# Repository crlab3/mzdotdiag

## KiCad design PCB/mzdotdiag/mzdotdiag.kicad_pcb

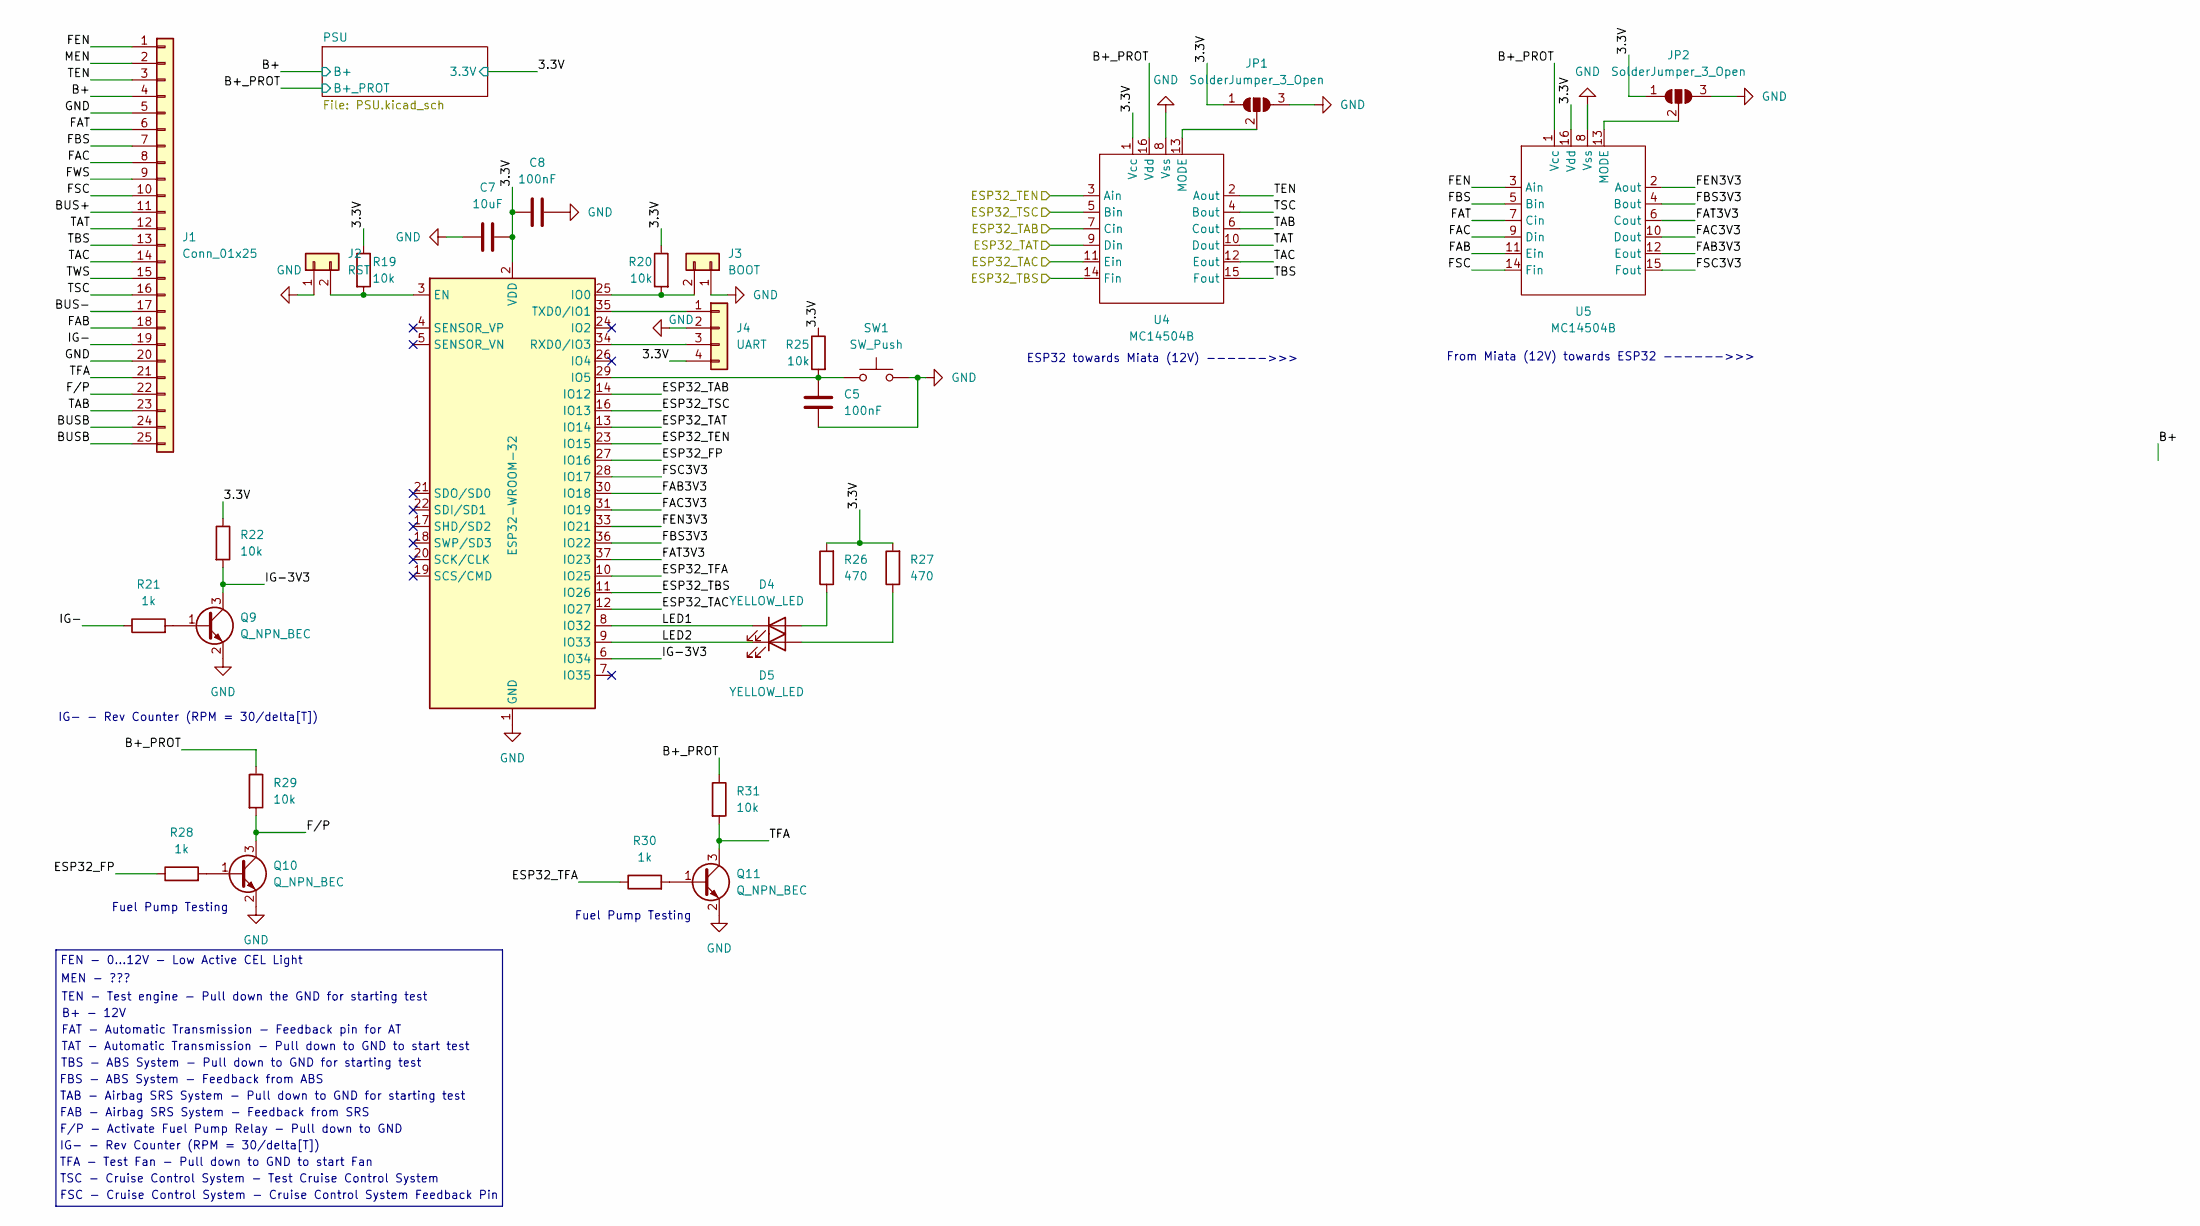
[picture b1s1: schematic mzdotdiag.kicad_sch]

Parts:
C5, C8: 100nF; C_0603_1608Metric
C7: 10uF; C_0805_2012Metric
D4, D5: YELLOW_LED; LED_0805_2012Metric
J1: Conn_01x25; MazdaNADiag; Mouser 651-1945193
J2: RST; SW_SPST_CK_RS282G05A3
J3: BOOT; SW_SPST_CK_RS282G05A3
J4: UART; PinHeader_1x04_P2.54mm_Vertical
JP1, JP2: SolderJumper_3_Open; SolderJumper-3_P1.3mm_Open_RoundedPad1.0x1.5mm
Q9, Q10, Q11: Q_NPN_BEC; SOT-23
R19, R20, R22, R25, R29, R31: 10k; R_0603_1608Metric
R21, R28, R30: 1k; R_0603_1608Metric
R26, R27: 470; R_0603_1608Metric_Pad0.98x0.95mm_HandSolder
SW1: SW_Push; SW_SPST_CK_RS282G05A3
U3: ESP32-WROOM-32; Mouser 356-ESP32WRM32E128PH
U4, U5: MC14504B; SOIC-16_3.9x9.9mm_P1.27mm; Mouser 863-NLV14504BDR2G

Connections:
/3.3V: C7.1, C8.1, J4.4, JP1.1 (A), JP2.1 (A), R19.1, R20.1, R22.1, R25.1, R26.2, R27.2, U3.2 (VDD), U4.1 (Vcc), U5.16 (Vdd); also elsewhere on the board
/B+: J1.4; also elsewhere on the board
/B+_PROT: R29.1, R31.1, U4.16 (Vdd), U5.1 (Vcc); also elsewhere on the board
/BUS+: J1.11
/BUS-: J1.17
/BUSB: J1.24, J1.25
/ESP32_FP: R28.1, U3.27 (IO16)
/ESP32_TAB: U3.14 (IO12), U4.7 (Cin)
/ESP32_TAC: U3.12 (IO27), U4.11 (Ein)
/ESP32_TAT: U3.13 (IO14), U4.9 (Din)
/ESP32_TBS: U3.11 (IO26), U4.14 (Fin)
/ESP32_TEN: U3.23 (IO15), U4.3 (Ain)
/ESP32_TFA: R30.1, U3.10 (IO25)
/ESP32_TSC: U3.16 (IO13), U4.5 (Bin)
/FAB: J1.18, U5.11 (Ein)
/FAB3V3: U3.30 (IO18), U5.12 (Eout)
/FAC: J1.8, U5.9 (Din)
/FAC3V3: U3.31 (IO19), U5.10 (Dout)
/FAT: J1.6, U5.7 (Cin)
/FAT3V3: U3.37 (IO23), U5.6 (Cout)
/FBS: J1.7, U5.5 (Bin)
/FBS3V3: U3.36 (IO22), U5.4 (Bout)
/FEN: J1.1, U5.3 (Ain)
/FEN3V3: U3.33 (IO21), U5.2 (Aout)
/FSC: J1.10, U5.14 (Fin)
/FSC3V3: U3.28 (IO17), U5.15 (Fout)
/FWS: J1.9
/F/P: J1.22, Q10.3 (C), R29.2
/IG-: J1.19, R21.1
/IG-3V3: Q9.3 (C), R22.2, U3.6 (IO34)
/LED1: D4.1 (K), U3.8 (IO32)
/LED2: D5.1 (K), U3.9 (IO33)
/MEN: J1.2
/TAB: J1.23, U4.6 (Cout)
/TAC: J1.14, U4.12 (Eout)
/TAT: J1.12, U4.10 (Dout)
/TBS: J1.13, U4.15 (Fout)
/TEN: J1.3, U4.2 (Aout)
/TFA: J1.21, Q11.3 (C), R31.2
/TSC: J1.16, U4.4 (Bout)
/TWS: J1.15
GND: C5.1, C7.2, C8.2, J1.5, J1.20, J2.1, J3.1, J4.2, JP1.3 (B), JP2.3 (B), Q9.2 (E), Q10.2 (E), Q11.2 (E), SW1.2, U3.1 (GND), U3.15 (GND), U3.38 (GND), U3.39 (GND), U4.8 (Vss), U5.8 (Vss); also elsewhere on the board
unnamed: D4.2 (A), R26.1
unnamed: D5.2 (A), R27.1
unnamed: J2.2, R19.2, U3.3 (EN)
unnamed: J3.2, R20.2, U3.25 (IO0)
unnamed: J4.1, U3.35 (TXD0/IO1)
unnamed: J4.3, U3.34 (RXD0/IO3)
unnamed: JP1.2 (C), U4.13 (MODE)
unnamed: JP2.2 (C), U5.13 (MODE)
unnamed: Q9.1 (B), R21.2
unnamed: Q10.1 (B), R28.2
unnamed: Q11.1 (B), R30.2
unnamed: C5.2, R25.2, SW1.1, U3.29 (IO5)

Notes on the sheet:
IG- - Rev Counter (RPM = 30/delta[T])
TBS - ABS System - Pull down to GND for starting test
B+ - 12V
FBS - ABS System - Feedback from ABS
TSC - Cruise Control System - Test Cruise Control System
F/P - Activate Fuel Pump Relay - Pull down to GND
FEN - 0...12V - Low Active CEL Light
TAT - Automatic Transmission - Pull down to GND to start test
TEN - Test engine - Pull down the GND for starting test
From Miata (12V) towards ESP32 ------>>>
FSC - Cruise Control System - Cruise Control System Feedback Pin
TFA - Test Fan - Pull down to GND to start Fan
TAB - Airbag SRS System - Pull down to GND for starting test
Fuel Pump Testing
FAT - Automatic Transmission - Feedback pin for AT
MEN - ???
FAB - Airbag SRS System - Feedback from SRS
ESP32 towards Miata (12V) ------>>>

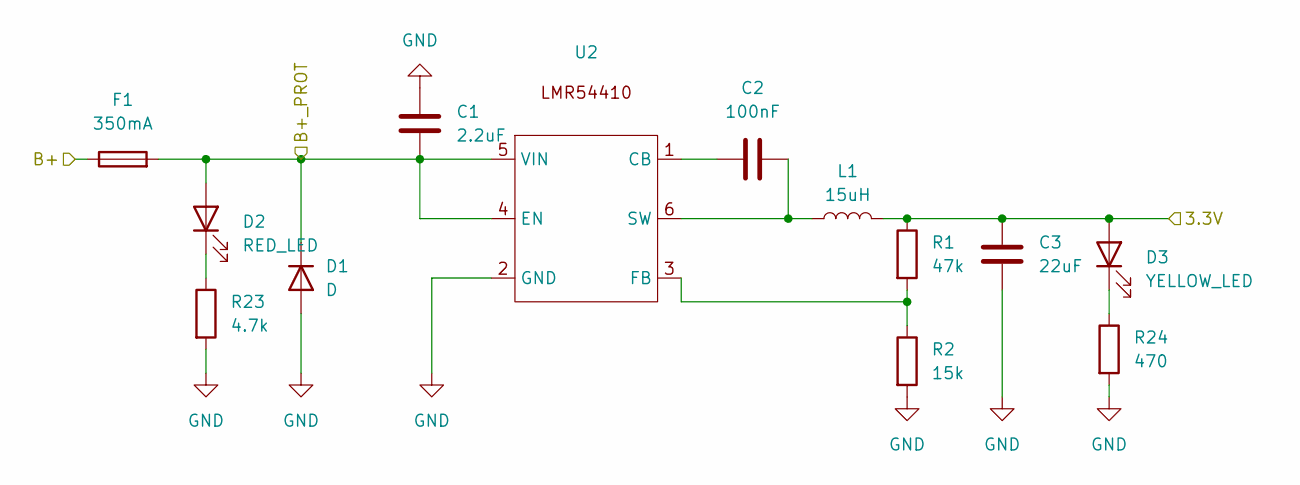
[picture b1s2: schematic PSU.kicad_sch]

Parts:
C1: 2.2uF; C_0805_2012Metric
C2: 100nF; C_0805_2012Metric
C3: 22uF; C_1210_3225Metric_Pad1.33x2.70mm_HandSolder
D1: D; D_SMB
D2: RED_LED; LED_0805_2012Metric
D3: YELLOW_LED; LED_0805_2012Metric
F1: 350mA; Fuse_1812_4532Metric_Pad1.30x3.40mm_HandSolder
L1: 15uH; L_Coilcraft_MSS7348-XXX
R1: 47k; R_0603_1608Metric_Pad0.98x0.95mm_HandSolder
R2: 15k; R_0603_1608Metric_Pad0.98x0.95mm_HandSolder
R23: 4.7k; R_0603_1608Metric_Pad0.98x0.95mm_HandSolder
R24: 470; R_0603_1608Metric_Pad0.98x0.95mm_HandSolder
U2: SOT-23-6_Handsoldering

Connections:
/3.3V: C3.1, D3.2 (A), L1.2, R1.1; also elsewhere on the board
/B+: F1.1; also elsewhere on the board
/B+_PROT: C1.2, D1.1 (K), D2.2 (A), F1.2, U2.4 (EN), U2.5 (VIN); also elsewhere on the board
GND: C1.1, C3.2, D1.2 (A), R2.2, R23.2, R24.2, U2.2 (GND); also elsewhere on the board
unnamed: D2.1 (K), R23.1
unnamed: D3.1 (K), R24.1
unnamed: C2.1, U2.1 (CB)
unnamed: R1.2, R2.1, U2.3 (FB)
unnamed: C2.2, L1.1, U2.6 (SW)

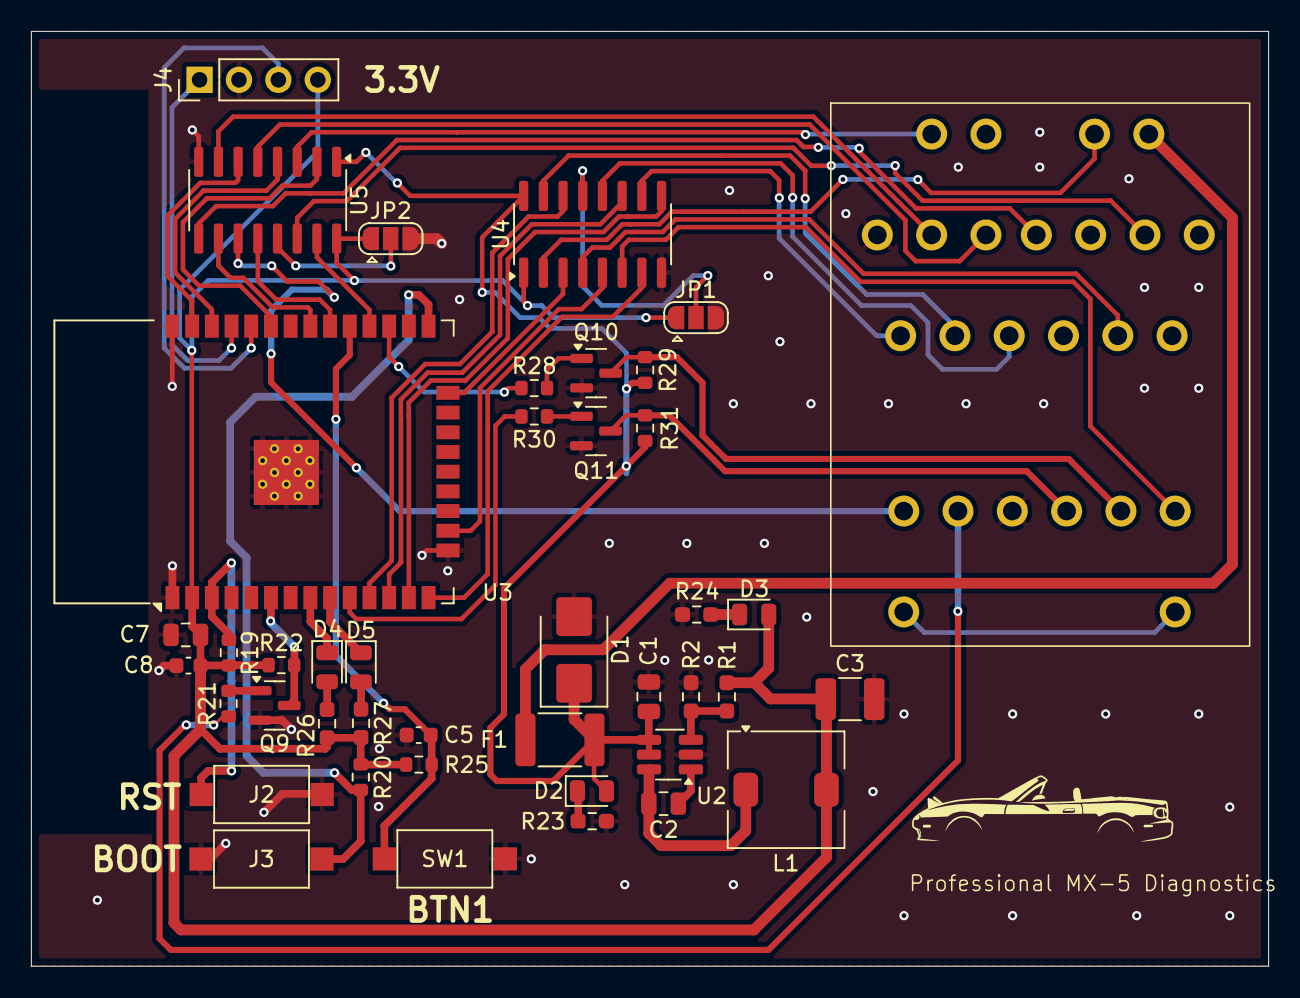
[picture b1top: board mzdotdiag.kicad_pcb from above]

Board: 2 copper layers, 79.8 x 60.3 mm, 42 parts (0 on the bottom side), 54 nets.

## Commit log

2025-04-02 uploaded first version of diagdump file
2025-04-03 Kicad project start, some components added
2025-04-03 advancements in schematic
2025-04-06 Schematic updates
2025-04-25 Lots of schematic updates, found CD4504B for logic level shifting
2025-04-28 schematic and pcb update with new levelshifter IC
2025-04-30 first commit from plugin
2025-04-30 updates to PCB
2025-04-30 pcb upd
2025-04-30 finished wiring
2025-05-01 some graphical updates
2025-05-06 order files and pcb done
2025-05-06 v1 order took place.
